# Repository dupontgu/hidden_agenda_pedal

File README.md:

# Hidden Agenda
 **A multi-effects pedal for your mouse and keyboard!**

 Have you ever wanted to add reverb to your mouse cursor and sending sailing gently accross your screen? Have you ever wished you could emphatically stomp on something to engage caps lock before ripping an angry email to your manager or tweeting at an airline? No? Well, I made this anyways.

 ## Contents
 * [How it works](#how-it-works) (at a high level)
 * [Full usage instructions](.docs/usage/)
 * [FAQ](.docs/faq/)
 * [Firmware Source Code](firmware/) (and build instructions)
 * [Electronics](hardware/) (schematic/board files)
 * [Enclosure](enclosure/) (CAD/Art)
 * [Alternate Usages](./circuitpython/) (use it as a MIDI controller!!)

 ### Shout-outs
 * Pedal artwork by [Ted Pioli](https://www.tedp.io/)
 * Pedal fabrication from [AmplifyFUN](https://amplifyfun.com/)

 ## How It Works

 The Hidden Agenda works as an HID interceptor. You plug your mouse/keyboard directly into the pedal, and then you plug the pedal into your computer via USB. The software on the pedal analyzes the data coming from the keyboard/mouse, applies some "signal processing" to it, and then forwards the processed data to the computer. When the pedal is off, it simply passes the keyboard/mouse data through without modifying it. It is a standalone unit and should not require any additional software to be installed on your computer - as far as it's concerned, the pedal is just a run-of-the-mill USB keyboard/mouse combo.

 ## What Effects Does It Have?

 The Hidden Agenda currently has 4 unique effects for mouse, and 4 for keyboard. They are mostly inspired by classic audio effects that you might find in a "real" pedal. Each effect has one parameter that can be tweaked with the onboard knob.

 ### Mouse Effects
 #### `1. Reverb`
 Send your cursor flying! This effect adds a bit of momentum to your mouse cursor, so when you stop moving your hand, it will keep going in the direction you were heading. When this effect is active, the knob controls the "length" of the reverb (or, how long it will take to slow down to a stop after you've stopped moving).

 #### `2. Looper`
 Record a gesture with your mouse and play it back on a loop. Hold the right mouse button down to record, move around as you please, and watch loop playback begin as soon as you release. Use the knob to adjust the playback speed of the loop. Turn it all the way up to play it at 2.5X speed, turn it all the way down to play at -2.5X (reversed!).

 #### `3. Distortion / Noise Filter`
 This is a two-in-one effect. Turn _up_ the knob (past halfway), and the pedal will add an increasing amount of random noise to your path of motion. Turn _down_ the knob, and the pedal will apply a low-pass filter to your motion, effectively smoothing it out. 

 #### `4. (Bonus) Crossover`
 Use your mouse as a keyboard! Use the scroll wheel to choose between characters, then tap the right mouse button to move on to the next. Hold the left mouse button + move left to backspace, move right to enter spaces, or move down to "hit" enter. You can also hold the right mouse button and move up/down to scroll through characters. The knob controls the speed at which the characters scroll.

 ### Keyboard Effects
 #### `1. Tremolo`
 Change the "volume" of your typing on a time interval. Imagine an imaginary hand pressing and releasing the shift key for you on a fixed schedule. Turn the knob up to increase the switch rate between upper/lowercase. If you turn the knob _all_ the way up, the effect will constanly force your typing to uppercase, effectively turning the pedal into a foot-powered caps lock button. If you turn the knob all the way down, the pedal will apply rANdOm/SarCaStiC case as you type.

 #### `2. Delay`
 Echo! (echo... echo...). This effect will repeat keystrokes on a time interval for you while it is engaged. The knob is divided into 4 zones, each corresponding to a delay interval time (from left to right: short, short-ish, long-ish, long). Within each zone, the knob controls the "feedback" - AKA the number of repetitions for a given keystroke. The rightmost edge of each zone will set the delay to repeat infinitely for maximum of 6 keys.

 #### `3. Pitch Shift / Harmonizer`
 Maps your keystrokes to... different keystrokes. The knob is divided into 3 sections. In the lowest section, the pedal will simply replace the keys you're pressing with those which are a fixed _"distance"_ away (by their [ascii number](https://www.asciitable.com/)). So if the distance is set to 1, and you press the 'a' key, the pedal will instead type 'b'. If the distance is set to 2, pressing 'a' would yield 'c', etc. You can increase the distance between characters by turning the knob up. As soon as you turn the knob into the second section (about 10 o'clock), the behavior changes slightly. Now, instead of a "pitch shift", this becomes a "harmony" - the orignal key you pressed will be typed, _as well as_ the shifted one. In other words, pressing one key will yield two typed characters. If you turn the knob into the third section (about 2 o'clock), the pedal will type 3 characters for each key you press: your original key character, one that is `n` characters away from that one, and another that is `n` characters away from the second. Think of it as a chord! You can turn up the knob _within_ each section to increase `n`.

 #### `4. (Bonus) Crossover`
 Use your keyboard as a mouse! The arrow keys move the cursor as you'd expect. The `enter` key emulates the mouse's left button. Use the letter keys to send the cursor flying in random directions. Yes, seriously. Modifier keys work as usual.

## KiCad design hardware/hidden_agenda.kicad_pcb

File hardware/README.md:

# Hidden Agenda Hardware

Check out an interactive version of this KiCAD project using [KiCanvas](https://kicanvas.org/?github=https://github.com/dupontgu/hidden_agenda_pedal/tree/main/hardware)!!

## BOM

_Most_ of the BOM is available in a [DigiKey parts list](https://www.digikey.com/en/mylists/list/27DUQKO28G), but please read the following notes:
* I have been purchasing the [potentiometer](https://guitarpedalparts.com/products/b5k-16mm-potentiometer-round-shaft-right-angle-pcb-pins), 
[SPDT toggle switch](https://guitarpedalparts.com/products/spdt-on-off-on-toggle-switch-solder-lugs), 
[footswitch](https://guitarpedalparts.com/products/momentary-spdt-foot-switch), and 
[knob cap](https://guitarpedalparts.com/products/small-fluted-knob-clear) on [GuitarPedalParts.com](https://guitarpedalparts.com/)
* For the LED, I use the [WS2812D-F5](https://datasheet.lcsc.com/lcsc/2204181500_Worldsemi-WS2812D-F5_C190565.pdf), which runs on 3.3V power and logic. These are easily sourced on eBay/AliExpress.

## USB Jack Caps

The [USB Jack Caps](./usb_caps_v6.stl) are 3D printed. I use a black, recycled PETG. They push into the side holes on the pedal and stabilize the USB ports (the whole PCB, really). They screw directly into the threaded inserts on the PCB using standard 8mm M3 screws.

## Assembly Notes

* All components are through-hole except for the XIAO RP2040 module.
* The boot button should be installed on the _bottom_ of the board.
* The threaded inserts should also be inserted and soldered from the bottom of the board. For safety, I have been taping over the holes on the top side as well.

## Schematic

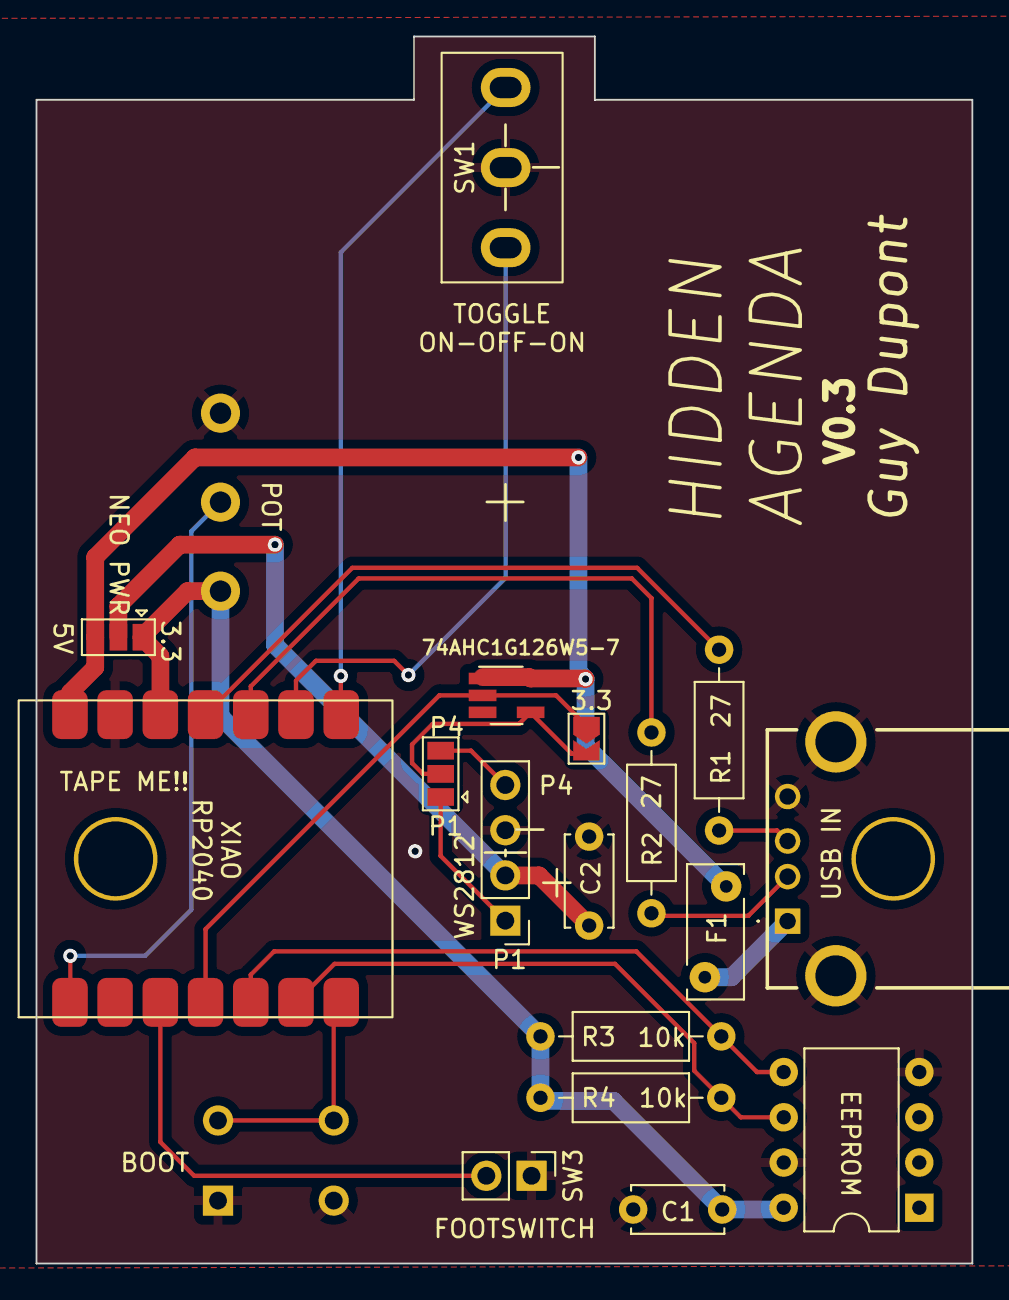
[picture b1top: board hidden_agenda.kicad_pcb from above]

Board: 2 copper layers, 52.6 x 68.9 mm, 19 parts (1 on the bottom side), 20 nets.

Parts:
C1, C2: C; C_Disc_D5.0mm_W2.5mm_P5.00mm
D1: WS2812B; PinHeader_1x04_P2.54mm_Vertical
F1: Polyfuse; Fuse_Bourns_MF-RHT050
J1: 1002-001-01000; 100200101000
JP1, JP2: Jumper_3_Open; SolderJumper-3_P1.3mm_Open_Pad1.0x1.5mm
JP3: Jumper_2_Open; SolderJumper-2_P1.3mm_Open_TrianglePad1.0x1.5mm
R1, R2: 27; R_Axial_DIN0207_L6.3mm_D2.5mm_P10.16mm_Horizontal
R3, R4: 10k; R_Axial_DIN0207_L6.3mm_D2.5mm_P10.16mm_Horizontal
RV1: R_Potentiometer; B5K_Potentiometer
SW1: SW_SPDT; GuitarPedalParts_SPDT
SW2: Boot Btn; SW_TH_Tactile_Omron_B3F-10xx
SW3: Footswitch; PinHeader_1x02_P2.54mm_Vertical
U1: MOUDLE-SEEEDUINO-XIAO; MOUDLE14P-SMD-2.54-21X17.8MM
U2: 24LC01; DIP-8_W7.62mm
U3: 74AHC1G126W5-7; SOT-23-5_HandSoldering

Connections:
+3.3V: C1.1, JP2.1 (A), R3.2, R4.2, RV1.1, U1.12 (3V3), U2.8 (VCC)
+5V: F1.2, JP2.3 (B), U1.14 (5V), U3.1 (OE), U3.5 (VCC)
FOOT_SW: SW3.2, U1.3 (PA10_A2_D2)
GND: C1.2, C2.2, D1.3 (VSS), J1.4 (GND), J1.MH1, J1.MH2, RV1.3, SW1.2 (B), SW2.1, SW3.1, U1.13 (GND), U2.4 (GND), U2.7 (WP), U3.3 (GND)
HOST_DM: J1.2 (D-), R2.2
HOST_DP: J1.3 (D+), R1.2
KNOB: RV1.2, U1.1 (PA02_A0_D0)
NEO: JP1.2 (C), JP3.2 (B), U3.4 (Y)
NEO_3V: JP3.1 (A), U1.4 (PA11_A3_D3), U3.2 (A)
NEO_P1: D1.1 (DOUT), JP1.1 (A)
NEO_P4: D1.4 (DIN), JP1.3 (B)
NEO_PWR: C2.1, D1.2 (VDD), JP2.2 (C)
unnamed: F1.1, J1.1 (V+)
unnamed: R2.1, U1.10 (PA5_A9_D9_MISO)
unnamed: R1.1, U1.11 (PA6_A10_D10_MOSI)
SCL: R4.1, U1.6 (PA9_A5_D5_SCL), U2.6 (SCL)
SDA: R3.1, U1.5 (PA8_A4_D4_SDA), U2.5 (SDA)
SOFT_BOOT: SW2.2, U1.7 (PB08_A6_D6_TX)
SW_0: SW1.1 (A), U1.9 (PA7_A8_D8_SCK)
SW_1: SW1.3 (C), U1.8 (PB09_A7_D7_RX)

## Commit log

2023-03-29 add passthrough fx, handling for weird mice reports?
2023-03-29 add tick to fx api, ensure timestamps available
2023-03-29 handle composite reports
2023-03-29 working first version of keyboard tremolo
2023-03-29 test sarcastic mode, fix dead zone for mode switching
2023-03-29 keyboard delay mostly working
2023-03-29 configure for v0 of hardware! get io working
2023-03-29 kill warnings
2023-03-29 migrate from examples directory
2023-03-29 change project name
2023-03-29 add first pass at kbd harmonizer
2023-03-29 buffer logs
2023-03-29 add support for 1-3 part harmonies
2023-03-29 add cdc reading
2023-04-06 add mouse reverb
2023-04-06 adjust color for mouse verb
2023-04-10 fix usb_descriptors for windows (phew)
2023-04-12 add proper serial number, vusb ids
2023-04-12 so thats how static works for function variables
2023-04-24 add mocked out persistence
2023-05-09 add abstraction, rough impl for mouse XOVER
2023-05-15 add mouse looper
2023-05-15 add eeprom persistence for board V2
2023-06-07 use pico pio lib from env variable, specify USB pin in application code
2023-06-09 create root fw directory
2023-06-09 add initial READMEs
2023-06-13 add reboot and brightness commands to repl
2023-06-13 rearrange util functions, move repl into own file
2023-06-14 refactor platform agnostic code into common lib, add test executable
2023-06-14 move all fx into common lib
2023-07-19 add raw hid logging
2023-07-19 add ability to change led colors to repl
2023-07-20 add option to reset to default settings
2023-07-20 add xosc startup delay
2023-07-20 setting up docs
2023-07-20 formatting
2023-07-20 faq docs
2023-07-24 add circuitpython examples and docs
2023-07-25 mouse xover work
2023-07-25 copyright stuff
2023-07-26 add setting for led flashing, add led pattern for kbd xover
2023-07-26 add keyboard crossover fx
2023-07-27 add repl docs
2023-07-27 ensure modifier keys get passed through for kbd xover
2023-07-28 add led pattern for mouse looping
2023-07-31 usage docs
2023-08-02 mouse xover usage improvements
2023-08-02 docs for firmware updating
2023-08-03 keyboard delay improvements
2023-08-03 add hardware files for rev3
2023-08-03 hardware/enclosure source files
2023-08-03 hardware assembly notes
2023-08-03 usb jack cap docs
2023-08-04 properly add xosc startup value to board def
2023-08-04 allow inversion of footswitch
2023-08-04 misc fixes
2023-08-04 go public?
2023-08-05 add git hash to build artifacts
2023-08-06 fallback to usage codes to determine protocol
2023-08-06 reorder fx, align docs
2023-08-06 fix cmd:flash docs
2023-08-07 DI for HidOutput interface, better logs
2023-08-07 add mouse report repl command
2023-08-07 route sidedoor mouse through main report callback
2023-08-07 add time-based sampling to reverb
2023-08-08 add docs for mouse command repl
2023-08-11 mouse downsampling, mouse speed level setting
2023-08-17 fix mouse accumulation, up version number
2023-08-18 add yt vid
2023-09-07 fix issue for devices that send multiple reports for keeb/mouse
2024-04-03 small qol improvements to test script
